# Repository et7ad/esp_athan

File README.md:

# Athan Clock (ESPHome on an ESP8266)

A small clock that calls the Athan at the exact times of your local mosque. It shows the time and the next prayer on a little screen, plays the Athan through a speaker, and takes its prayer times from tiny JSON files that live in this repository (or any other repository in case you want to replicate the project on your own), one file per day per mosque. This project was built because I could not find one that follows my own mosque's timetable and keeps working when I move.

**Who should read what**

| You are... | Read | Why |
|---|---|---|
| **Someone who already has a device** | **Section 1 only.** | Everything you need to set it up should be in this section. |
| Someone who wants to build one | Section 2 | Parts, wiring, PCB, 3D printed case, preparing the memory card. Needs soldering and a bit of patience. |
| Someone who wants to add a mosque's timetable, or host the data yourself | Section 3 | How the prayer times are stored and served. |
| Someone who wants to change how the firmware behaves | Section 4 and `DEVELOPER.md` | The code is one ESPHome file; the internals are documented there. |

---

## 1. You have the device in your hands

Setting it up is two steps. One, you connect it to your home Wi‑Fi. After that, everything is set from a web page that the clock itself shows on your phone or computer. You can alternatively use the two buttons on the front to do the same things (I think the web page is faster though).

### 1.1 First power‑up: connect it to your Wi‑Fi (once)

1. Plug it in and wait > **2 to 3 minutes**.
2. On your laptop (or phone), open the Wi‑Fi list. A network called **`AthanFallbackHotspot`** appears. Join it with the password **`athan404`**.
3. A page opens by itself asking for your home Wi‑Fi. If it does not, open a browser and go to `192.168.4.1`.
4. Pick your home Wi‑Fi (or enter its SSID manually), type its password, save.
5. The clock restarts, joins your Wi‑Fi, sets its own time from the internet, downloads today's prayer times, and shows the time and the next prayer. From then on it does this by itself every day.

You do this **once**. The clock keeps the Wi‑Fi you gave it, together with all your other settings, in its own memory: unplug it, move it to another socket, leave it off for a month, plug it back in, and it reconnects to the same network by itself. The hotspot only comes back when you want a different network (see below) or when the network it knows is not there.

Two things to know:

- The clock only sees **2.4 GHz** Wi‑Fi networks. Most home routers have one; if yours shows two networks (for example "home" and "home‑5G"), pick the one without "5G".
- If you move it to another home, just plug it in: when it cannot find the Wi‑Fi it knows, it opens the `AthanFallbackHotspot` network by itself after two or three minutes, and you repeat steps 2 to 4. However, if you want to make it **forget** a Wi‑Fi when that network is still in range (for example to move the clock to a different network in the same home): plug it in **while holding both front buttons**, then let go. Within a little while the LED blinks twice, the clock restarts, and the hotspot appears.

### 1.2 Set everything from the web page

On a phone or computer connected to the same Wi‑Fi, open a browser and go to:

**`http://athan.local`**

If that address does not open (it depends on your phone and router, and Android phones usually cannot open `.local` names), use the clock's own IP address instead: on the device use the two buttons, press **Select** (the upper button), then press **Next** (the lower button) until the screen says **Info**, press **Select** again, and the screen shows an address like `192.168.1.42`. Type that into the browser. Your router's app or admin page also lists it, under the name `athan`. (optional): You usually can tell your router to always give the clock the same address (this is often called "DHCP reservation" or "static lease") and bookmark it.

<table><tr>
<td></td>
<td></td>
</tr></table>

The page is organised in groups:

- **Location** – your mosque. Pick it from the list and the clock downloads that mosque's timetable and time zone. The list of mosques is in section 3.4; if yours is missing, ask me and I will add it.
- **Athan Audio** – which athan-recording is used for Dhuhr, Asr, Maghrib and Isha. Changing it plays a 20‑second preview.
- **Fajr Athan Audio** – which athan-recording is used for Fajr. Also previews.
- **Volume** and **Fajr Volume** – the Fajr Athan has its own volume, so it can be gentler at dawn (or more loud if you want to count on it to wake you up 😴).
- **Hourly Tick** – an optional short sound at the top of every hour, and **Tick Window Start / End** to allow it only during part of the day. The tick plays at every full hour from Start up to, but not including, End: with Start 7 and End 22 it ticks at 7:00, 8:00 … 21:00 and stays quiet at night. The window can be any stretch of the day, including one that runs through midnight: set Start *higher* than End (for example Start 22, End 7) and it ticks from 22:00 through the night until 6:00. On the page that simply means the upper slider sits higher than the lower one. Start equal to End means all day. You can completely turn the tick off by choosing **None** for the sound.
- **Fajr / Dhuhr / Asr / Maghrib / Isha Athan** – five switches to turn the call off for a particular prayer. The clock still shows and counts down to that prayer; it just stays silent. Visual cue: if the Athan is off, the next prayer name on the screen is partially str~~icken~~-thr~~oug~~
- **12‑hour Clock** – show `5:04 PM` instead of `17:04`.
- **Buttons Locked** – makes the two front buttons do nothing except silence the sound (I guess mainly for kids?). See 1.3 for how to unlock without the page.
- **Stop Audio** – silences whatever is playing right now.
- **Next Prayer**, **Today's Times**, **Athan Playing** – just information.
- **Check For Update / Install Update** – firmware updates, see 1.4.
- **Restart**, **External Relay**, **IP Address**, **Free Heap**, **Reset Reason** – restart the clock; switch the relay output if you connected something to it; the address to type in your browser; and two numbers for degbugging purposes that I may ask you for if something goes wrong.

Anything you change on the page takes effect immediately, and the page always shows what the clock is currently doing, even if it was changed with the buttons.

### 1.3 The screen and the two buttons

The screen normally shows three lines: the time and date, the next prayer and its time, and how long until it. A small padlock in the bottom‑right corner means the buttons are locked. A crossed circle with a **W** means the clock has lost Wi‑Fi (it keeps working; it just cannot download tomorrow's times until Wi‑Fi is back).

The two buttons:

- **Select** (upper) – opens the menu. Inside the menu it confirms. While the Athan is playing it silences it.
- **Next** (lower) – inside the menu it moves to the next item. On the normal screen it silences the Athan if one is playing; otherwise it toggles the relay output.

The menu closes by itself after a minute without presses. Its items, in order:

| Item | What it does |
|---|---|
| Athan | choose the recording for Dhuhr, Asr, Maghrib, Isha (Next previews, Select keeps) |
| Fajr Athan | choose the recording for Fajr (previews at the Fajr volume) |
| Athan On/Off | Next moves through Fajr, Dhuhr, Asr, Maghrib, Isha; Select flips one on or off; Select on **Done** leaves |
| Hourly Tick | choose the hourly sound, or None |
| Tick Window | Next moves between Start, End and Done; Select on Start or End lets Next change the hour; Select again confirms. The third line always shows how long the window is. Start above End means the window runs through midnight |
| Location | your mosque |
| Update | first Select checks for a new firmware, second Select installs it |
| Volume | Next lowers by 10 % (wraps around to 100 %), a tone plays at the new level, Select keeps |
| Fajr Volume | the same, for Fajr |
| Clock | Select flips between 24h and 12h |
| Lock Buttons | Select locks the buttons and returns to the clock |
| Info | firmware version, the clock's IP address and its `athan.local` name |
| Cancel | back to the clock |
| Q | an advanced option that is **off** by default. If it is ever **ON** press select to turns it off |

To **unlock** the buttons without the web page: unplug the clock, then plug it back in while holding **one** of the two buttons (either one). The LED blinks three times quickly and the buttons work again.

### 1.4 Living with it

- **At prayer time** the Athan plays and the LED stays on for a few minutes. Either button, or **Stop Audio** on the page, silences it. Sunrise and Doha are shown but never call.
- **Fajr** uses its own recording and its own volume, the ones you chose under Fajr Athan Audio and Fajr Volume.
- **Firmware updates** need no cable. On the page press **Check For Update**; if a newer version exists, **Install Update**. On the device: menu, **Update**, Select twice. The clock restarts by itself when done.
- **No screen?** The clock works without it: it still calls the Athan and serves the web page. If you plug a screen in later it comes alive within about 10 seconds.
- **Speaker too quiet?** The board has a jack for an external powered speaker (any small PC speaker with its own power). Plug it in and flip the small speaker switch on the board so only the external one is used.

### 1.5 If something is off

- **`athan.local` does not open.** Use the IP address instead (section 1.2). Android in particular never opens `.local` names. Some routers also answer `http://athan/` or `http://athan.lan/`.
- **The buttons do nothing.** Look for the padlock in the corner: the buttons are locked. Switch **Buttons Locked** off on the page, or unplug and replug while holding one button.
- **The sound is wrong: nothing plays, several clips play one after another, the wrong recording, or it keeps playing on its own.** The audio module inside is probably a clone of a common MP3 player and occasionally gets confused, most often right after a button press. The firmware already avoids the usual triggers, but when it happens the fix is simple: **unplug the power and plug it back in.** That is all it needs.
- **The screen is dark or frozen.** Screens clones occasionally lock up; unplug and replug fixes them too. If you unplugged the screen yourself while the clock was running, plugging it back in is handled once; a second time needs a power cycle. The clock keeps calling the Athan meanwhile.
- **The time or the prayer times look wrong.** Check the Wi‑Fi mark on the screen and the **Location** on the page, then press **Refresh Prayer Times**. The clock can only download times when it is online; if it has been offline for more than a day it keeps yesterday's times until it reconnects.
- **You want to see the last restart reason or the memory.** They are the last two rows on the page. If **Reset Reason** ever says `Exception`, tell me; it is not expected.

### 1.6 Home Assistant (optional)

If you run Home Assistant, add the clock through the ESPHome integration; it is discovered automatically. When asked for the key, use:

`jAOYf5QQGoONCqGQnC7fwPhSeb/ZTUTlawp1Lvu63ZI=`

Everything on the web page becomes an entity in Home Assistant: the selects, sliders, switches, buttons and readouts. The **External Relay** switch is handy for things like the IoT power strip below, to switch an amplifier or a light with the Athan.

That is the end of what a device owner needs. The rest of this page is for people building, feeding or changing the clock.

---

## 2. Building your own device

For people who are comfortable with basic electronics and 3D printing and want to assemble a unit from scratch. You will end up with the same device described in section 1.

### 2.1 Parts

- ESP8266 D1 Mini (or an ESP‑12 module, as on the PCB).
- DFPlayer Mini MP3 module with a microSD card.
- SSD1306 128×64 I2C OLED display.
- Two momentary push buttons (Next, Select).
- Optional relay module on `GPIO13`.
- 5 V input, 3.3 V regulator for the ESP8266, a speaker or an external powered speaker on the jack.

The parts list with pictures is in `BOM.md`, which points at the KiCad‑generated BOM files under `hardware/pcb/athan_kicad/BOM/`.

### 2.2 Wiring

`WIRING.md` has the full pin table and decoupling notes. In short:

- OLED on I2C: `GPIO4` (SDA), `GPIO5` (SCL); reset on `GPIO16` (only 7/8‑pin modules have it).
- DFPlayer on the hardware UART: `GPIO1` (TX) and `GPIO3` (RX), powered from 5 V.
- Built‑in LED on `GPIO2`.
- Next on `GPIO14`, Select on `GPIO12`, both with the ESP's internal pull‑ups.
- Relay on `GPIO13`.

A breadboard build works with the same pins.

### 2.3 PCB and enclosure files

- KiCad project (schematic, layout, settings): `hardware/pcb/athan_kicad/`. Renders: `hardware/pcb/athan_kicad/generated_imgs_and_3d/`.
- Enclosure (STL, STEP, Fusion, and a ready gcode): `hardware/encolsure/Iteration13/`. There are top halves for a round or a rectangular speaker and for two display variants; pick the pair that matches your parts.

The PCB accepts several OLED footprints: an 8‑pin header, two 4‑pin I2C footprints with the two common pin orders (`GND‑VCC‑SCL‑SDA` and `VCC‑GND‑SCL‑SDA`; match your module's silkscreen), and a 7‑pin SPI footprint that the firmware does not use.

### 2.4 Flashing the first time

The DFPlayer shares the UART pins that are also used for programming, so the order matters:

1. Solder the ESP module, the power parts and the headers. **Do not solder the DFPlayer yet.**
2. Connect a 3.3 V USB‑to‑serial adapter (CP2102, CH340, FT232...) to the programming pins: `GND` to `GND`, adapter TX to `ESP_RX`, adapter RX to `ESP_TX`, 3.3 V to `ESP_VCC`. Never feed 5 V into `ESP_VCC`.
3. Hold `GPIO0` to `GND` while powering up; that puts the ESP8266 into its serial bootloader.
4. Flash the firmware. Either build it yourself from `firmware/athan.yaml` with ESPHome (you need a `secrets.yaml` next to it with `wifi_ssid` and `wifi_password`), or flash a released `.bin` with `web.esphome.io` in a supported browser, or any ESP8266 flashing tool.
5. Now solder the DFPlayer.

From the second PCB revision on, the DFPlayer's UART lines pass through a small solder jumper, bridged by default. If you ever need the serial header again with the DFPlayer already in place, cut the jumper, flash, and bridge it again with a blob of solder.

### 2.5 Flashing afterwards (no cable)

- From the device: menu, **Update** (checks `docs/firmwareinfo/latest.json` in this repo, then installs).
- From the web page: **Check For Update** and **Install Update**, or the **OTA Update** form at the bottom of the page where you pick a `.bin` file. In Safari on macOS the file picker greys out `.bin` files; use Chrome, or from a terminal:

  ```bash
  curl -F "update=@/path/to/firmware.bin" http://athan.local/update
  ```

- From the ESPHome dashboard or CLI (`esphome run firmware/athan.yaml`).
- If the clock is in its `AthanFallbackHotspot` mode, `http://192.168.4.1` also offers a firmware upload.

If you host your own firmware for the in‑device update, the `.md5` file next to the `.bin` must contain only the checksum string, nothing else.

### 2.6 Preparing the memory card

The DFPlayer does not care about file names; it numbers files by the **order they were copied** to the card. So the card better be written by the script, not by drag and drop.

1. Put the card in the computer (Mac or Linux). Everything on it will be erased, whatever its name or content.
2. Put the audio files in one folder on your computer, named as in the table below.
3. Open `scripts/sd_card_cpy_script.sh` and set `SRC` to that folder. On a Mac also set `DEST` to the mounted card (for example `/Volumes/AUDIO`); on Linux leave `DEST` alone.
4. Run it in a terminal: `bash scripts/sd_card_cpy_script.sh`. On Linux it lists the removable disks, asks which one is the card, and asks for your password once. Answer `YES` when it asks to erase and format the card. It then copies the files, cleans up, reads the card back the way the DFPlayer reads it, and prints the 48 tracks in the order the module will see them.
5. The last lines must say **Card is good** and then **Card ejected**. Do not mount the card on the computer again; put it in the DFPlayer and power the clock. If the script says **PROBLEM** instead, run it again and let it format.

| Files | Names | What they are |
|---|---|---|
| 1–10 | `A1`–`A10` | Athan recordings, regular wording |
| 11–20 | `B1`–`B10` | hourly tick sounds |
| 21–24 | `C1`–`C4` | short tones used by the menu (22 = volume tone, 23 = click) |
| 25–34 | `D1`–`D10` | audio used by the advanced `Q` option |
| 35–44 | `F1`–`F10` | Athan recordings with the Fajr wording (`F<k>` is usually the same reciter as `A<k>`; if a reciter has no Fajr recording, copy `A<k>` again as `F<k>`) |
| 45–48 | `Z_fallback_1`–`4` | a short "please restart" message that plays if the DFPlayer counts files wrongly; must be last |

Cards made for firmware V5 or older lack the `F` files and must be redone for V6. Cards made for V6 before the current script can be missing Fajr athans 7–10 and the fallback message for the DFPlayer (see below) and should be redone with the current script.

Why the script formats and checks: on a Mac, every file written to a card of this kind gets a hidden twin named `._name.mp3`, which the script has to delete again, and every deleted twin leaves two dead slots in the card's table of contents. With 48 files that table needs 165 slots. A card formatted the usual way (Disk Utility's default for cards up to 8 GB) has room for only 128 slots in the first block of that table, and the DFPlayer never reads past the first block: the Mac shows all 48 files, but for the module Fajr athans 7–10 and the fallback message do not exist. So the script formats the card with large blocks (1024 slots), keeps Spotlight and the file‑event logger off the card (two tiny marker files it leaves behind on purpose), and at the end trusts only what it reads back from the card, not what Finder shows. If you ever see `._` files on the card, run the script again and let it format rather than deleting them by hand. Linux makes no twins, but a card keeps every leftover of its earlier life until it is formatted, so the script erases and checks there too.

To look at a card without changing anything, for example one that plays nothing or the wrong thing for some number, run:

```bash
INSPECT=yes bash scripts/sd_card_cpy_script.sh
```

It prints the tracks exactly as the DFPlayer counts them, with a note on every entry that the module cannot reach.

### 2.7 3D printing

PLA is fine indoors; PETG or ABS for a warm spot. 0.2 mm layers, 3 to 4 perimeters, 15 to 25 % infill. Print the top and bottom with their flat faces on the bed. Supports are rarely needed if you set the overhang angle to 80° and the horizontal expansion to about 0.8 mm (maybe inside the big side openings and under the crescent).

Thanks to [Ahmed Nader](https://github.com/iNader) for guidance on component placement and to [Omar Ramadan](https://github.com/omarramadan913) for participating in the enclosure 3D design.

---

## 3. Prayer‑time data

For people who want to add a mosque's timetable, correct one, or host the data themselves. The clock never calculates prayer times; it reads them from small text (JSON) files, so it always matches what your mosque publishes.

### 3.1 Where the data lives

By default the firmware reads the `docs/` folder of this repository, served over plain HTTP through the [raw.githack](https://raw.githack.com) mirror (GitHub itself is HTTPS only, which this small chip does not do):

- Time zone per mosque: `docs/timezones/<key>.json`, containing `{ "TZ": "..." }`.
- Daily times: `docs/athantimes/<key>/<year>/<DDD>.json`, one file per day, `DDD` being the day of the year with three digits (`001.json` is January 1st).
- Firmware pointer: `docs/firmwareinfo/latest.json`.

The URLs the firmware builds are `http://rawcdn.githack.com/et7ad/esp_athan/master/docs/timezones/<key>.json` and `http://rawcdn.githack.com/et7ad/esp_athan/master/docs/athantimes/<key>/<year>/<DDD>.json`.

### 3.2 File format

The exact rules are in [prayertimes_specs.md](prayertimes_specs.md); follow it to the letter, the firmware is a small parser. In short: one JSON object per day, every value a string, times as `HH:MM` with leading zeros. Example:

```json
{
  "year": "2025", "month": "1", "#": "Wednesday", "day": "1",
  "fajr": "06:05", "fajr_iqa": "06:30",
  "sunrise": "07:22", "doha": "07:37",
  "dhuhar": "12:15", "dhuhar_iqa": "12:35",
  "asr": "02:44", "asr_iqa": "03:15",
  "maghrib": "05:04", "maghrib_iqa": "05:09",
  "isha": "06:19", "isha_iqa": "08:00"
}
```

The time‑zone file uses the POSIX form, for example `{ "TZ": "PST8PDT,M3.2.0,M11.1.0" }`. Find yours in the [posix_tz_db](https://github.com/nayarsystems/posix_tz_db/blob/master/zones.csv) list; the `Continent/City` form does not work reliably on this chip.

`scripts/break_json.py` turns a whole‑year source file into the daily files, filling missing iqama fields with an offset and computing Doha as sunrise plus 15 minutes. `scripts/santaclara_prayer_times_parser.py` extracts a year from the MCA PDF timetable. The Davis data comes from Dr. Albara Ramli's site (<https://albara.ramli.net/ar/>).

### 3.3 The list of mosques in the firmware

The mosque keys live in exactly one place in `firmware/athan.yaml`: the `options:` list of the **Location** select. The Location menu, the web page and the URLs all read it. The order is what the clock remembers, so existing entries are never moved or removed; new mosques replace the `masjidN` placeholders.

| Slot | Key | Mosque | Map |
|---|---|---|---|
| 1 | `davis` | Islamic Center of Davis, times from Dr. Albara Ramli's site matching his [Iqamah Times](https://albara.ramli.net/iqamah/) app | https://maps.app.goo.gl/TS9X4CXDYKfkRHph6 |
| 2 | `sclaramca` | Muslim Community Association (MCA), Santa Clara, times from [mcabayarea.org](https://www.mcabayarea.org) | https://maps.app.goo.gl/86ttxawSJ9t7fXnEA |
| 3 | `sclaraalnoor` | Masjid Al‑Noor, Santa Clara, times from [mcabayarea.org](https://www.mcabayarea.org) | https://maps.app.goo.gl/ZAGiTFhHkNFhijHBA |
| 4 | `sacramento` | Sacramento area mosque (to be detailed) | |
| 5 | `cairo` | Cairo profile (to be detailed) | |
| 6 | `woodland` | Woodland Mosque, <https://woodlandmosque.com> | https://maps.app.goo.gl/cv6gB9eWJYny81SWA |
| 7–14 | `masjid7`…`masjid14` | placeholders | |
| 15 | `masjid15` | Visalia, California, times from [IslamicFinder](https://www.islamicfinder.org/) (adhan official; iqama and Doha derived); steps in `docs/athantimes/masjid15/README.md` | |

I intend, God willing, to keep the files for these mosques up to date. If you would like a placeholder slot used for your mosque, open an issue or contact me with the details.

### 3.4 Hosting the data yourself

1. Create a repository (or any HTTP server) with the same layout: `docs/timezones/<key>.json` and `docs/athantimes/<key>/<year>/<DDD>.json`.
2. Generate the daily files (adapt `scripts/break_json.py`).
3. In `firmware/athan.yaml`, change the two base URLs (in the `change_location_handler` and `load_prayer_times` scripts) to your host.
4. Build and flash (section 2.4 or 2.5).

---

## 4. Changing the firmware

For people who want to change how the clock behaves. The whole firmware is one ESPHome file, `firmware/athan.yaml`; there is no other source code. Build and flash with:

```bash
# needs a secrets.yaml next to the yaml with wifi_ssid and wifi_password
esphome run firmware/athan.yaml
```

`DEVELOPER.md` explains the internals: the globals and scripts, how the next prayer is computed, how the downloads are parsed, the menu state machine, the web entities, and the limits of the ESP8266 (memory and the saved‑settings store) that shape several decisions. `todo.md` lists planned hardware changes.

A few things worth knowing without opening that file:

- Every control on the web page is also a plain HTTP call, useful for scripts and phone shortcuts:

  ```bash
  curl -X POST http://athan.local/button/stop_audio/press
  curl -X POST "http://athan.local/number/volume/set?value=40"
  curl -X POST "http://athan.local/select/athan_audio/set?option=Athan%203"
  curl -X POST http://athan.local/switch/fajr_athan/turn_off
  curl -X POST "http://athan.local/select/location/set?option=woodland"
  curl http://athan.local/text_sensor/next_prayer
  ```

  `scripts/relay_control.sh` and `scripts/relay_control_native.py` do this for the relay.
- The device's log can be streamed to the web page by setting `log: true` under `web_server:` in the yaml (off by default to save memory).
- The Home Assistant API can be turned off in the yaml to free memory; the comment above the `api:` block says what you lose.

---

## 5. Why this exists, and similar projects

I wanted the Athan called reliably at the times my own mosque uses, without reprogramming anything when I move or give a clock to a friend. Everything mosque‑specific lives in data files in Git, so the same device follows any timetable. It is ESPHome rather than a hand‑written Arduino sketch, so it plugs into Home Assistant and benefits from ESPHome's updates.

Two projects that do more, differently (Good effort MashaAllah):

- [Muslim Prayer Time (Solat Time) on ESP32](https://fornextlife.wordpress.com/2021/03/07/muslim-prayer-time-on-esp32/) uses an online prayer‑time API, an LCD and a browser configuration page.
- [Islamic Prayer Times on an ESP32 TTGO T‑Display](https://www.instructables.com/Islamic-Prayer-Times-ESP32-TTGO-T-Display/) finds your position through Google APIs and shows a map and the qibla on a colour screen.

Both compute or fetch times from services; this one plays exactly what your mosque publishes.

---

## 6. Getting a unit, contributing, license

If you would like a clock but do not want to build one, reach out through the repository. If I have spare parts I am happy to build one for free; otherwise you can cover the components and I will assemble and flash it, whenever I find the time ;-;

Bugs, ideas, or a mosque to add: open an issue. The project is MIT licensed; fork it, adapt it, extend it as you like.

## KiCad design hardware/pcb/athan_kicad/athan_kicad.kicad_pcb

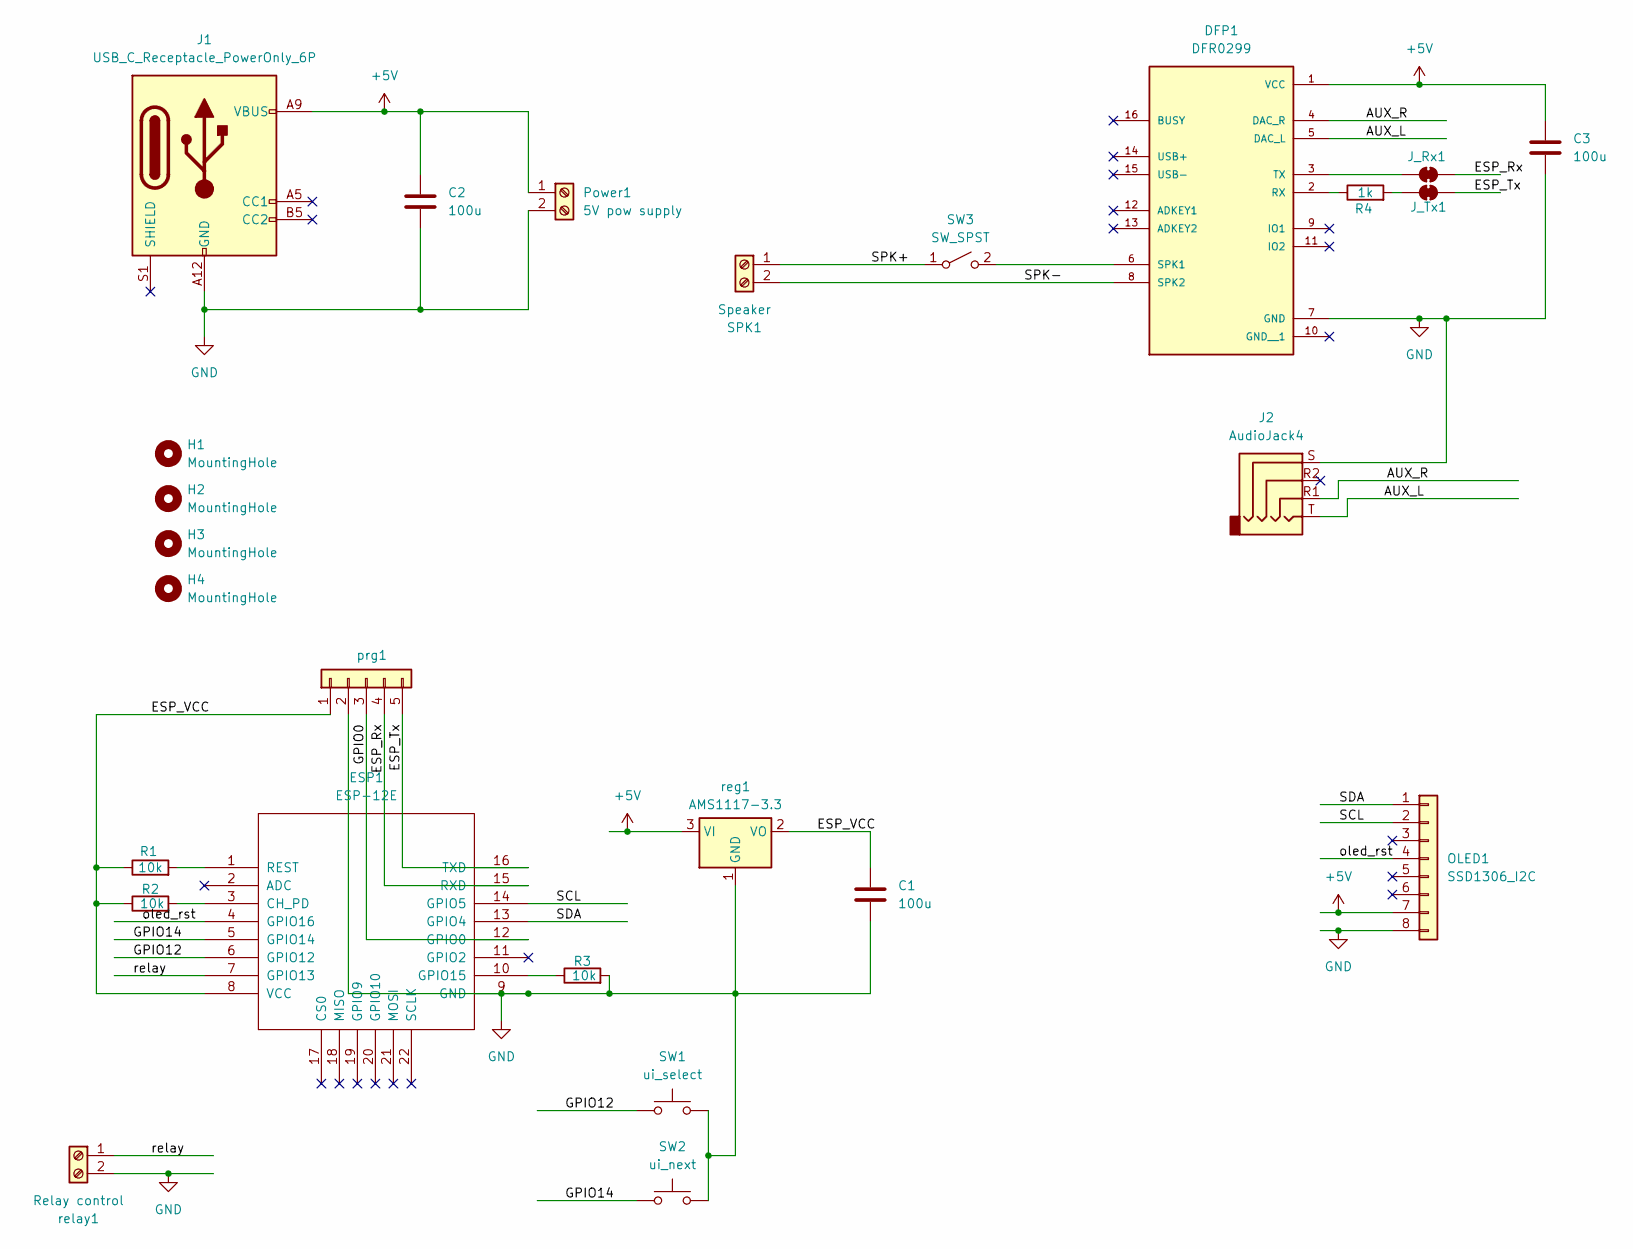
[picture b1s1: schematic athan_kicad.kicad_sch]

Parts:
C1, C2, C3: 100u; CP_Radial_D10.0mm_P5.00mm_P7.50mm
DFP1: DFR0299; MODULE_DFR0299
ESP1: ESP-12E; ESP-12E_SMD
H1, H2, H3, H4: MountingHole; MountingHole_3.2mm_M3
J1: USB_C_Receptacle_PowerOnly_6P; USB_C_Receptacle_GCT_USB4125-xx-x_6P_TopMnt_Horizontal
J2: AudioJack4; Jack_3.5mm_PJ320A_Horizontal
J_Rx1: SolderJumper_2_Bridged; SolderJumper-2_P1.3mm_Bridged2Bar_RoundedPad1.0x1.5mm
J_Tx1: SolderJumper_2_Bridged; SolderJumper-2_P1.3mm_Bridged2Bar_RoundedPad1.0x1.5mm
OLED1: SSD1306_I2C; Adafruit_SSD1306_multi
Power1: 5V pow supply; TerminalBlock_MaiXu_MX126-5.0-02P_1x02_P5.00mm
R1, R2, R3: 10k; R_Axial_DIN0207_L6.3mm_D2.5mm_P7.62mm_Horizontal
R4: 1k; R_Axial_DIN0207_L6.3mm_D2.5mm_P7.62mm_Horizontal
SPK1: Speaker; TerminalBlock_MaiXu_MX126-5.0-02P_1x02_P5.00mm
SW1: ui_select; SW_SPST_Omron_B3F-40xx
SW2: ui_next; SW_SPST_Omron_B3F-40xx
SW3: SW_SPST; SW_Slide-03_Wuerth-WS-SLTV_10x2.5x6.4_P2.54mm
prg1: Conn_01x05; PinHeader_1x05_P2.54mm_Vertical
reg1: AMS1117-3.3; SOT-223-3_TabPin2
relay1: Relay control; TerminalBlock_MaiXu_MX126-5.0-02P_1x02_P5.00mm

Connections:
+5V: C2.1, C3.1, DFP1.1 (VCC), J1.A9 (VBUS), J1.B9 (VBUS), OLED1.7, Power1.1, reg1.3 (VI)
/AUX_L: DFP1.5 (DAC_L), J2.T
/AUX_R: DFP1.4 (DAC_R), J2.R1
/ESP_Rx: ESP1.15 (RXD), J_Rx1.2 (B), prg1.4
/ESP_Tx: ESP1.16 (TXD), J_Tx1.2 (B), prg1.5
/ESP_VCC: C1.1, ESP1.8 (VCC), R1.1, R2.1, prg1.1, reg1.2 (VO)
/GPIO0: ESP1.12 (GPIO0), prg1.3
/GPIO12: ESP1.6 (GPIO12), SW1.1
/GPIO14: ESP1.5 (GPIO14), SW2.1
/SCL: ESP1.14 (GPIO5), OLED1.2
/SDA: ESP1.13 (GPIO4), OLED1.1
/SPK+: SPK1.1, SW3.1 (A)
/SPK-: DFP1.8 (SPK2), SPK1.2
/oled_rst: ESP1.4 (GPIO16), OLED1.4
/relay: ESP1.7 (GPIO13), relay1.1
GND: C1.2, C2.2, C3.2, DFP1.7 (GND), ESP1.9 (GND), J1.A12 (GND), J1.B12 (GND), J2.S, OLED1.8, Power1.2, R3.2, SW1.2, SW2.2, prg1.2, reg1.1 (GND), relay1.2
unnamed: DFP1.2 (RX), R4.1
unnamed: DFP1.6 (SPK1), SW3.2 (B)
unnamed: DFP1.3 (TX), J_Rx1.1 (A)
unnamed: ESP1.3 (CH_PD), R2.2
unnamed: ESP1.10 (GPIO15), R3.1
unnamed: ESP1.1 (REST), R1.2
unnamed: J_Tx1.1 (A), R4.2

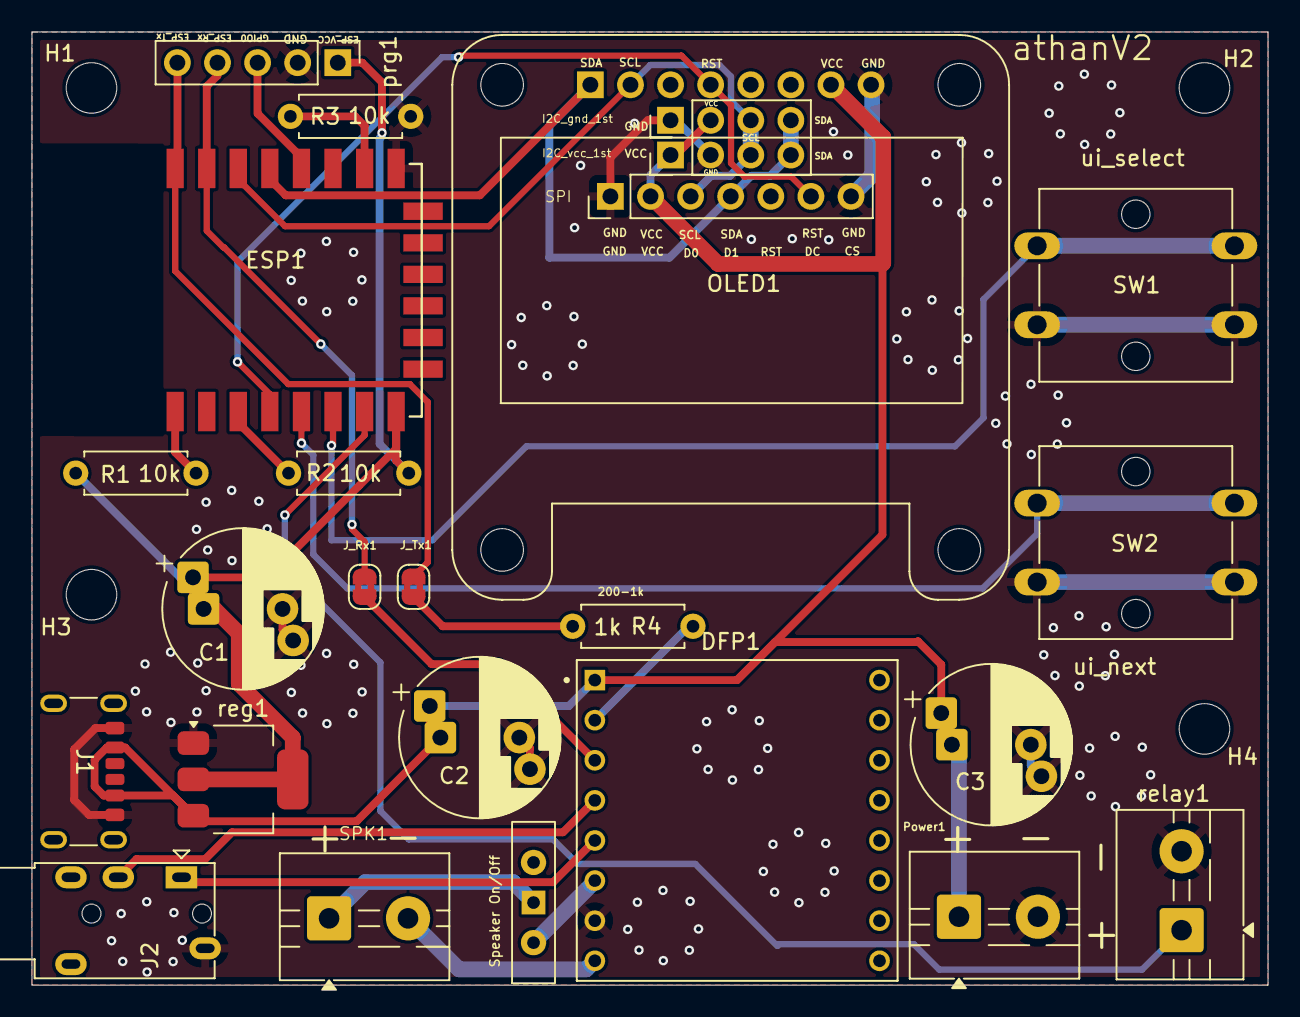
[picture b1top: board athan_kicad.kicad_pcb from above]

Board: 2 copper layers, 78.3 x 60.4 mm, 26 parts (0 on the bottom side), 23 nets.

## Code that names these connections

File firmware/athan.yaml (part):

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  oled_flip_x: "true"      # ESPHome default true; set both flips to false to rotate the screen 180 degrees
  oled_flip_y: "true"
  oled_contrast: "1.0"     # 0.0 .. 1.0
  oled_reset_pin: "16"     # GPIO16 to the module's RES pin if it has one (4-pin modules do not); pulsed by ESPHome at every setup

  # ---------------------------------------------------------------
  # NOTE for people just changing the OLED / SSD1306 display
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captive_portal:

i2c:
  sda: GPIO4
  scl: GPIO5
  scan: true

uart:
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    id: "ui_next"
    internal: true
    pin:
      number: GPIO14
      mode: INPUT_PULLUP
      inverted: true
    on_press:
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    id: "ui_select"
    internal: true
    pin:
      number: GPIO12
      mode: INPUT_PULLUP
      inverted: true
    on_press:
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  - platform: gpio
    id: external_relay
    name: "External Relay"
    pin: GPIO13
    restore_mode: RESTORE_DEFAULT_OFF
    web_server:
      sorting_group_id: grp_system
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  # # # for testing with RPI:
  # - platform: gpio
  #   id: gpio0_output
  #   pin: GPIO0
  #   inverted: false

http_request:
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
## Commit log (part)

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2025-12-01 directories change
2025-12-02 update url provided dynamically
2025-12-02 if up to date no need to check url
2025-12-02 fixing urls
2025-12-02 Add prayer times for December 22, 2026
2025-12-02 fixing hour tick menu
2025-12-02 flip screen vertically option commented, also making athan select menu similar to hourly tick
2025-12-02 y not v
2025-12-02 default flipped so making false optinal
2025-12-02 flip would require both x and y or neither to keepp orientation
2025-12-03 making internal entities internal
2025-12-03 Add prayer times for December 3, 2025
2025-12-03 for testing Update dhuhar prayer time to 12:40
2025-12-03 for testing Change dhuhar prayer time to 12:50
    Updated dhuhar prayer time from 12:40 to 12:50.
2025-12-04 testing: Update dhuhar prayer time format
2025-12-04 testing, changing asr to hourly time
2025-12-05 testing Update asr prayer time from 04:00 to 04:07
2025-12-05 test bug Update asr prayer time to 04:30
2025-12-05 bug testing Update asr prayer time to 04:36
2025-12-05 test after bug fixing Update maghrib prayer time to 05:10
2025-12-05 fixed bug testing ..
2025-12-05 test bug fix
2025-12-05 bug fix athan wasnt playing when matching a Htick
2025-12-09 fixing screen address
2025-12-09 restore from flash on
2025-12-09 dummy wifi reset network to force into captive portal - bug fix
2025-12-10 fallback password added in README
2025-12-10 updating binaries
2025-12-10 adding fallback hostpot password
2025-12-10 suggesting power strip and 'Q:' notice
2025-12-10 timezones adjusted, only davis prayertimes added
2025-12-10 sd_card_cpy_script.sh helper added
2025-12-10 external speaker notice
2025-12-11 PCB schematic updated with fixes of the previous version. The Layout is not done yet. Check the previous commit for a previous version layout
2025-12-11 explain the uart conflict in README
2025-12-12 was ignoring .lib by mistake
2025-12-12 PCB V2 in progress
2025-12-13 enhancing schematic: adding 1k resistor before dfplayer Rx for eleminating potential buzzing. changing AUX jack footprint from PJ320E to PJ320A which is a mirrored image (more available on stores). P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
2025-12-13 athanV2 PCB finished (hopefully)
2025-12-13 fixing a couple fo labels
2025-12-13 follow up
2025-12-13 helping screenshots
2025-12-16 randomization added to advanced feature Q
2025-12-17 santa clara MCA and Alnoor added with parsing script
2025-12-17 update readme masjid table
2025-12-17 updating gitignore
2025-12-17 api notice and binaries updated
2025-12-19 firmware V2: using rawcdn instead of raw urls for production avoiding redirects with unlimited traffic. updated the binaries and build as well
2025-12-20 add img
2025-12-22 handling the dfplayer mini glitch of playing all files in burst then keep playing the last one... by adding fallback audio files at the end asking for a manual restart
2025-12-30 readme adding enclosure and acknowledgement
2026-01-01 MCA and Alnoor santa clara 2026 added
2026-01-03 3D of enclosure finally Added!!
2026-01-03 enclosure 3D few changes for better fit
2026-01-03 shhh
2026-01-04 Enclosure iteration 13, fixing the height of the roundspeaker enclosure, adding chamfers for more friendly 3D printing, and minor other fixes
2026-02-22 next button toggles output when not in menu and no athan playing
2026-02-23 relay control wihtout homeasssistant
2026-03-19 bug fix: adding dfplayer debounce and fixing back to back comms, hopefully this fixes the getting stuck bug.
2026-03-19 quickie, removing unncessary display update
2026-03-19 20ms is enough 100 isnt needed
2026-03-19 hardware/software changes todo in next version
2026-05-01 woodland for first time: added 2026 adn 2027, davis added 2027. json breaking script for albara data updated to compensate for doha and iqa times
2026-05-01 added woodland mosque to the yaml and timezone + markdowns update
2026-05-01 we at version 5 after adding woodland
2026-05-01 removing the builds folder in firmware. It makes more sense to only maintian the yaml file and then esphome can be easily used to produces the binaries/build files
2026-05-17 prayer times plots added
2026-05-17 adding index page for prayer times plots
